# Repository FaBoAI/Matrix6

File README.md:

# Matrix Six

ESP32-S3-WROOM-1-N8R8を使った、Matrix5シールド向けのKiCad 10開発基板です。現行設計は **v0.8（2層・四隅R2 mm）**。内層配線を表裏へ移し、USBとGNDを再設計しました。オートルーターは使わず、部品配置と配線を個別に指定しています。

## KiCadで開く

[Matrix6.kicad_pro](hardware/Matrix6/Matrix6.kicad_pro)をKiCad 10で開いてください。KiCad標準のシンボル・フットプリント・3Dモデルライブラリをインストールし、同じフォルダーの `DevBoard.pretty` と `fp-lib-table` を一緒に保管します。動作確認版はKiCad 10.0.6です。

- ESP32-S3-WROOM-1-N8R8、ネイティブUSB-C、TPS63001によるUSB／LiPo両対応3.3 V電源。
- 裏面microSD（CS=10、MOSI=11、CLK=12、MISO=13）。口はアンテナ側へ向け、15.8 × 22.5 mmの抜き差し空間を確保。
- 裏面JST-PH 2ピンLiPo端子、MCP73831で公称100 mA充電、AO3401AによるUSB／電池自動切替。
- USBの左にRESET、右にBOOT。基板下部の赤LEDは `POWER`、青LEDはGPIO48の `PIN 48`。
- 40.64 × 61.00 mm、四隅R2 mm、2層FR4・公称1.6 mm・両面1 oz。USBは表面のみ・ビア0。表面のUSB両脇にGNDを確保し、表裏のGNDベタをビアで接続。
- H1/H2は各20ピン、ピッチ2.54 mm、列間33.02 mmのメスソケット。1番ピンはUSB側。
- 表面中央に大きな `Matrix Six`（文字高2.0 mm）、その直下に `Designed by GPT-6 Astra`（0.8 mm）。

## Matrix5シールドとの互換性

[Matrix5](https://github.com/FaBoAI/Matrix5)のMainとS1〜S11の実設計から端子情報を読み取り、全40位置と各シールドの使用信号を照合しました。**38端子の割り当てを合わせ、H2.20はVBAT**です。H2.5 / H2.6はNC（Matrix5のUSB D− / D＋）で、確認した11シールドはいずれも使用していません。

[端子表・シールド別照合・取り付け条件](docs/matrix5-compatibility.md)を参照してください。XY位置と使用ピンは一致していますが、積層高さ、アンテナ周辺、通電動作は実機での確認が必要です。USB-UART機能は追加していません。SDはシールドのSPI/I2C用GPIO11〜13を共有するため、競合する使い方ではカードを抜いてください。

電源計算の条件は周囲50℃、**3.3 V合計500 mA（MCU・SDを含む）＋VBUSシールド負荷100 mA＋充電100 mA**です。H1.1/H2.1は出力専用で、H2.1へ外部給電するとUSBへ逆給電できます。大電流のLED全点灯・コイル・ヒーターはこの条件に含みません。GPIOは3.3 Vで、S1用5 Vレベル変換はありません。

LiPoは保護回路付き1セル3.7 V／満充電4.2 V、500 mAh以上・放電定格1 A以上を基準とします。J3は**1番BAT+、2番GND**。同じJST形状でも電池側の極性を確認してください。電池動作中のH2.1に5 Vは出ません。セル温度センサーは搭載していません。

## 検証と図面

| 項目 | 保存したv0.8の結果 |
|---|---|
| DRC / ERC / 未配線 / 回路図整合性 | すべて0件 |
| 外形 | 四隅R2 mm、直線4本＋円弧4本で閉じた輪郭 |
| SD抜き差し空間 | 裏面15.8 × 22.5 mm、部品の配置禁止領域。重なり0 |
| Matrix5端子照合 | 全11シールドの使用ピン・40位置が一致 |
| USB | 表面のみ・ビア0、A/B両側とも幾何学的な長さ差0.01 mm未満 |
| USB本体下 | 表面配線・ビア・ベタ0。禁止領域の負の試験でも検出を確認 |
| USB直線部の表面GND | 両脇の幅0.5 mmを各1,563点検査、欠損0 |
| 電源降下の計算 | 3.3 V・500 mAでモジュールまで49.9 mV、H1まで27.9 mV |
| GND帰路のDC計算 | モジュール帰路500 mAで2.34 mV、入力帰路800 mAで6.45 mV |
| 最小ドリル | 0.3 mm。U1放熱穴はパッド0.8 mm、環状幅0.25 mm |

- [回路図](docs/validation/schematic.png) / [表面配線](docs/validation/pcb-top.png) / [裏面配線](docs/validation/pcb-bottom.png) / [SD抜き差し図](docs/validation/sd-access.svg)
- [DRC](docs/validation/drc.json) / [ERC](docs/validation/erc.json) / [シールド照合](docs/validation/matrix5-compatibility.json)
- [USB禁止領域](docs/validation/usb-keepout-validation.json) / [配線・電源計算](docs/validation/electrical-audit.json) / [GND計算](docs/validation/ground-plane-dc.json)
- [2層化の設計・検証範囲](docs/matrix-six-v08.md) / [USB断面計算](docs/analysis/two-layer-usb.json) / [表面GND検査](docs/validation/two-layer-ground.json)
- [検証対象CADのSHA-256](docs/validation/cad-sha256.json) / [回路図と30°3Dの並列表示](docs/validation/schematic-and-3d.png)

USBの均一断面は幅0.38 mm・線間0.18 mm・表面GNDとの間隔0.20 mm。FR4のεr=4.5を仮定した2D計算は約90.3 Ωです。裏面GNDは信号配線で4領域に分かれ、表面とビアで接続されており、連続した裏面参照プレーンではありません。USBの主な帰路は表面の両脇GNDとして設計しています。A側の長さにはR11のパッド間1.65 mmを含みます。

JLCPCB標準2層での管理インピーダンス保証は前提にしていません。断面・DC・配線温度の結果は設計計算であり、局所的な曲がりや長さ調整、コネクタを含むUSBの実測保証ではありません。試作機でUSB両挿し向き、SI/EMC、SD同時動作、給電切替・負荷・温度を確認します。

## JLCPCBへの試作発注

[v0.8の2層版製造データ](manufacturing/v0.8/README.md)を使用してください。48部品・26 BOMグループの型番は継承していますが、部品移動と表裏変更があるため **CPLもv0.8へ差し替えが必要**です。U1/U2等の放熱・パッド内ビアには充填と銅キャップを要求しており、両面実装費も残ります。最終削減額は新しい見積もりで確認してください。

既存のv0.7注文は4層版のデータです。v0.8の製造データとの混用はできません。部品在庫、実装位置・極性、CAMの確認が必要で、この作業では支払い・製造承認は行っていません。

JLCPCBに見積時点のGerberをアップロードし、基板5枚のWeb表示額は **$83.27**（部品・実装・送料別）でした。旧4層注文の$120.47から約31%減ですが、条件を最適化した4層比較額$86.68との差は約4%です。[見積もり内訳と条件](docs/analysis/two-layer-v08-quote.md)

## 検証の再実行

```sh
python3 scripts/verify_project.py
```

リポジトリをgit cloneして実行してください。設計ルール・互換性・外形の比較にはgit履歴が必要です。KiCad CLIと `pcbnew` / `wx` を使えるPythonが必要です。macOSの標準KiCadインストールは自動選択します。他の環境では `KICAD_CLI` と `KICAD_PYTHON` を指定してください。`ANALYSIS_PYTHON` にNumPy / SciPy / Shapely / Matplotlibを導入したPythonを指定すると、表裏を接続したGNDのDC計算も再実行します。検証はゾーンを再充填してPCBを保存し、レポートを更新するため、GUI上の編集を先に保存してください。

`scripts/manual_matrix5_layout.py` は初期インポートのコミットを入力とした、座標指定による移行記録です。オートルーターではありません。再実行すると後からのCAD編集を上書きするので、通常の検証には使いません。

v0.6の回路選定・電源条件は [設計メモ](docs/matrix-six-v06.md) に記録しています。

v0.7の外形変更は `scripts/round_board_corners.py`、v0.8の2層化は `scripts/redesign_two_layer.py` と `scripts/two_layer_routes.py` に記録しています。後者は `f12c10f` の4層CADから座標指定の変更を再生し、現在のCADを上書きするため通常の検証には使いません。v0.8の [外形検証](docs/validation/rounded-corners.json) はR2輪郭の保持と0.3 mm最小穴を確認します。版別の製造出力はPCBのリビジョンから出力先を決定します。

旧DevBoardの資料は [docs/devboard-v04](docs/devboard-v04/README.md) に履歴として保存しています。現在の端子・給電条件はこのREADMEとv0.6の互換性資料を使用してください。ライブラリの帰属は [THIRD_PARTY_NOTICES.md](THIRD_PARTY_NOTICES.md) に記載しています。

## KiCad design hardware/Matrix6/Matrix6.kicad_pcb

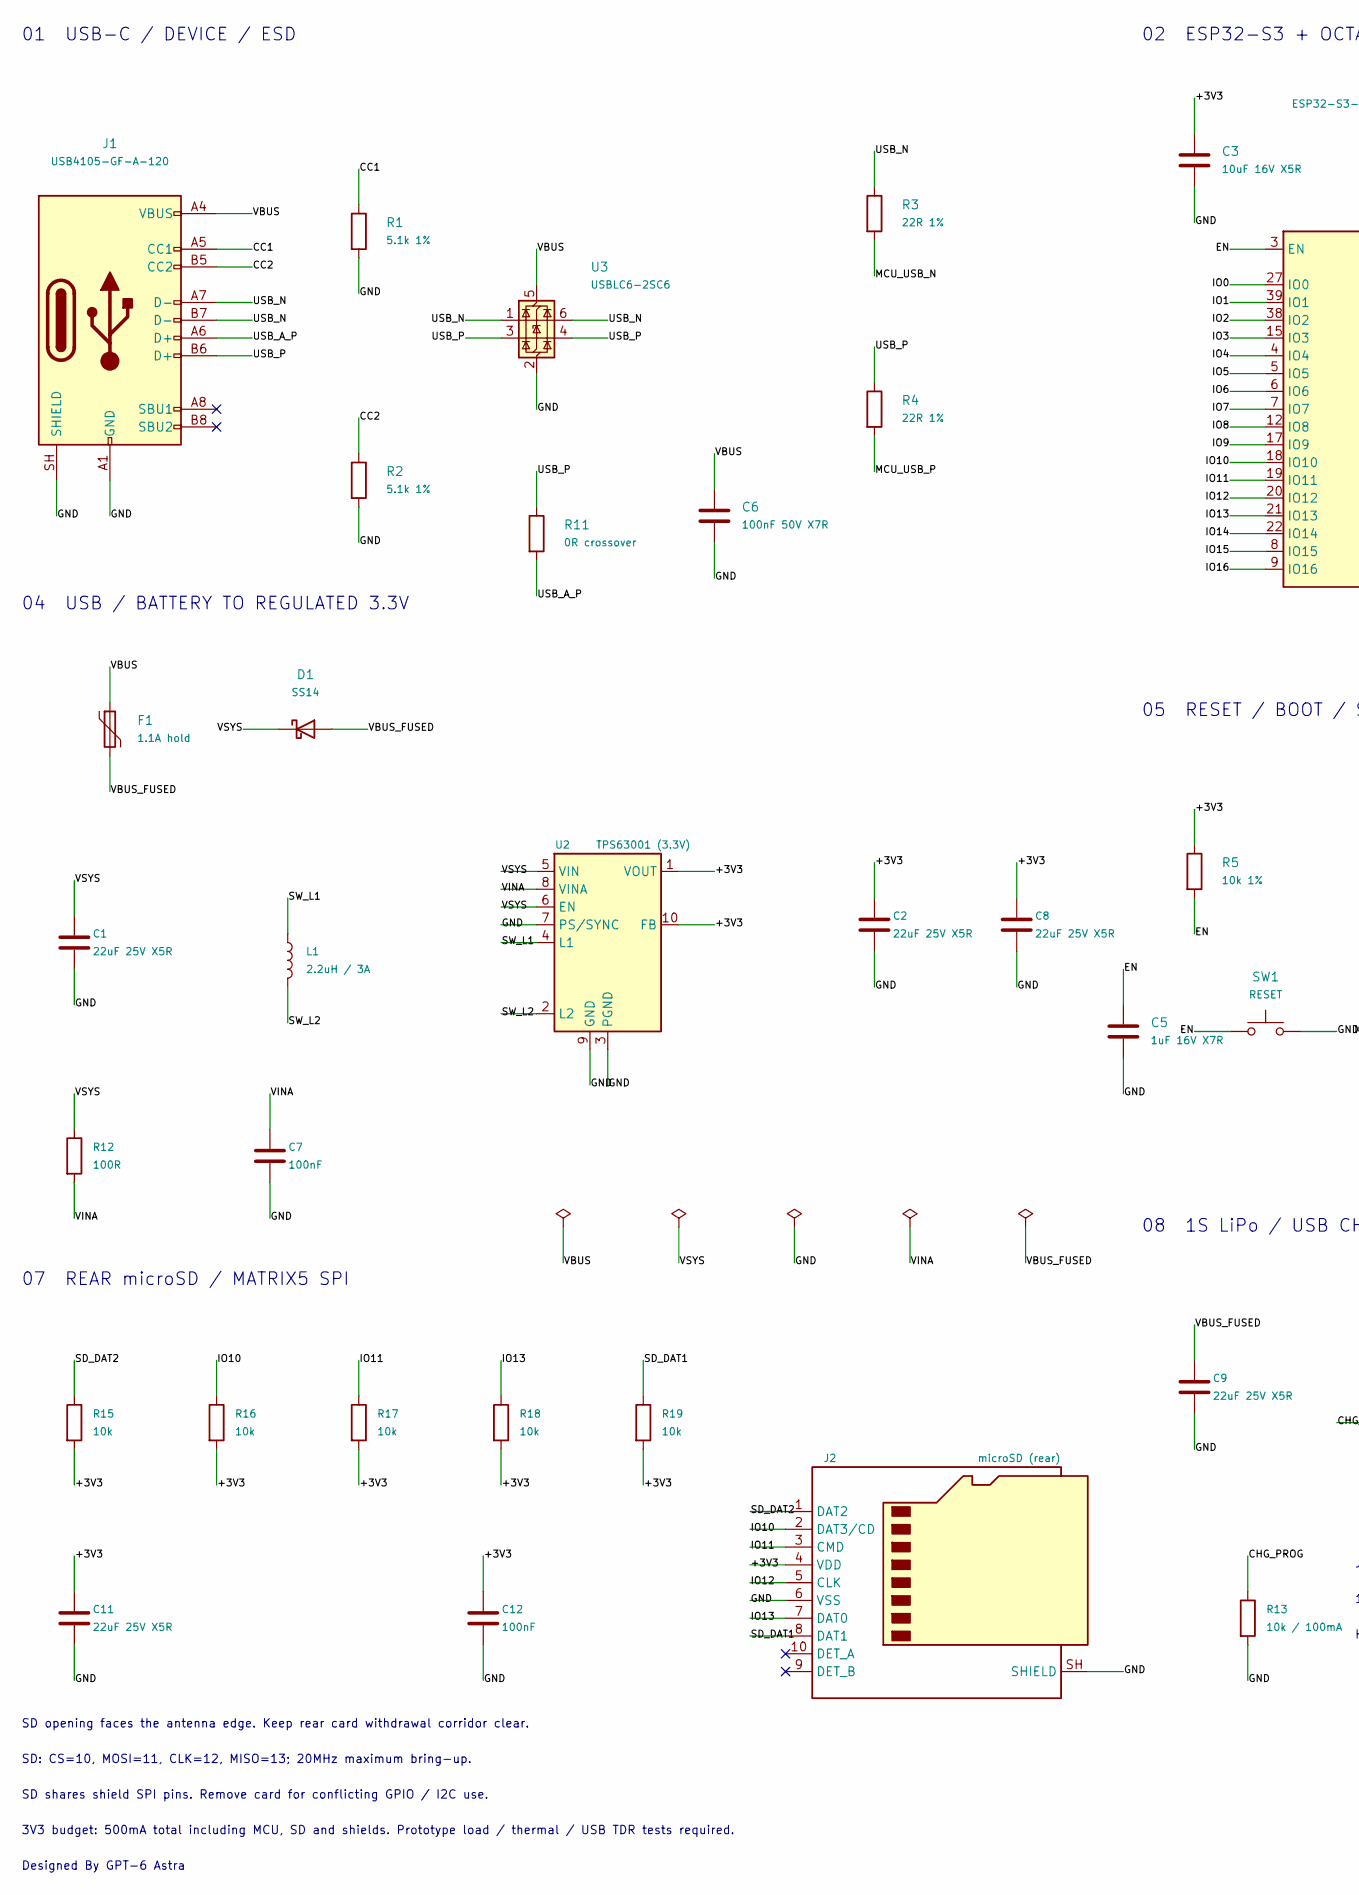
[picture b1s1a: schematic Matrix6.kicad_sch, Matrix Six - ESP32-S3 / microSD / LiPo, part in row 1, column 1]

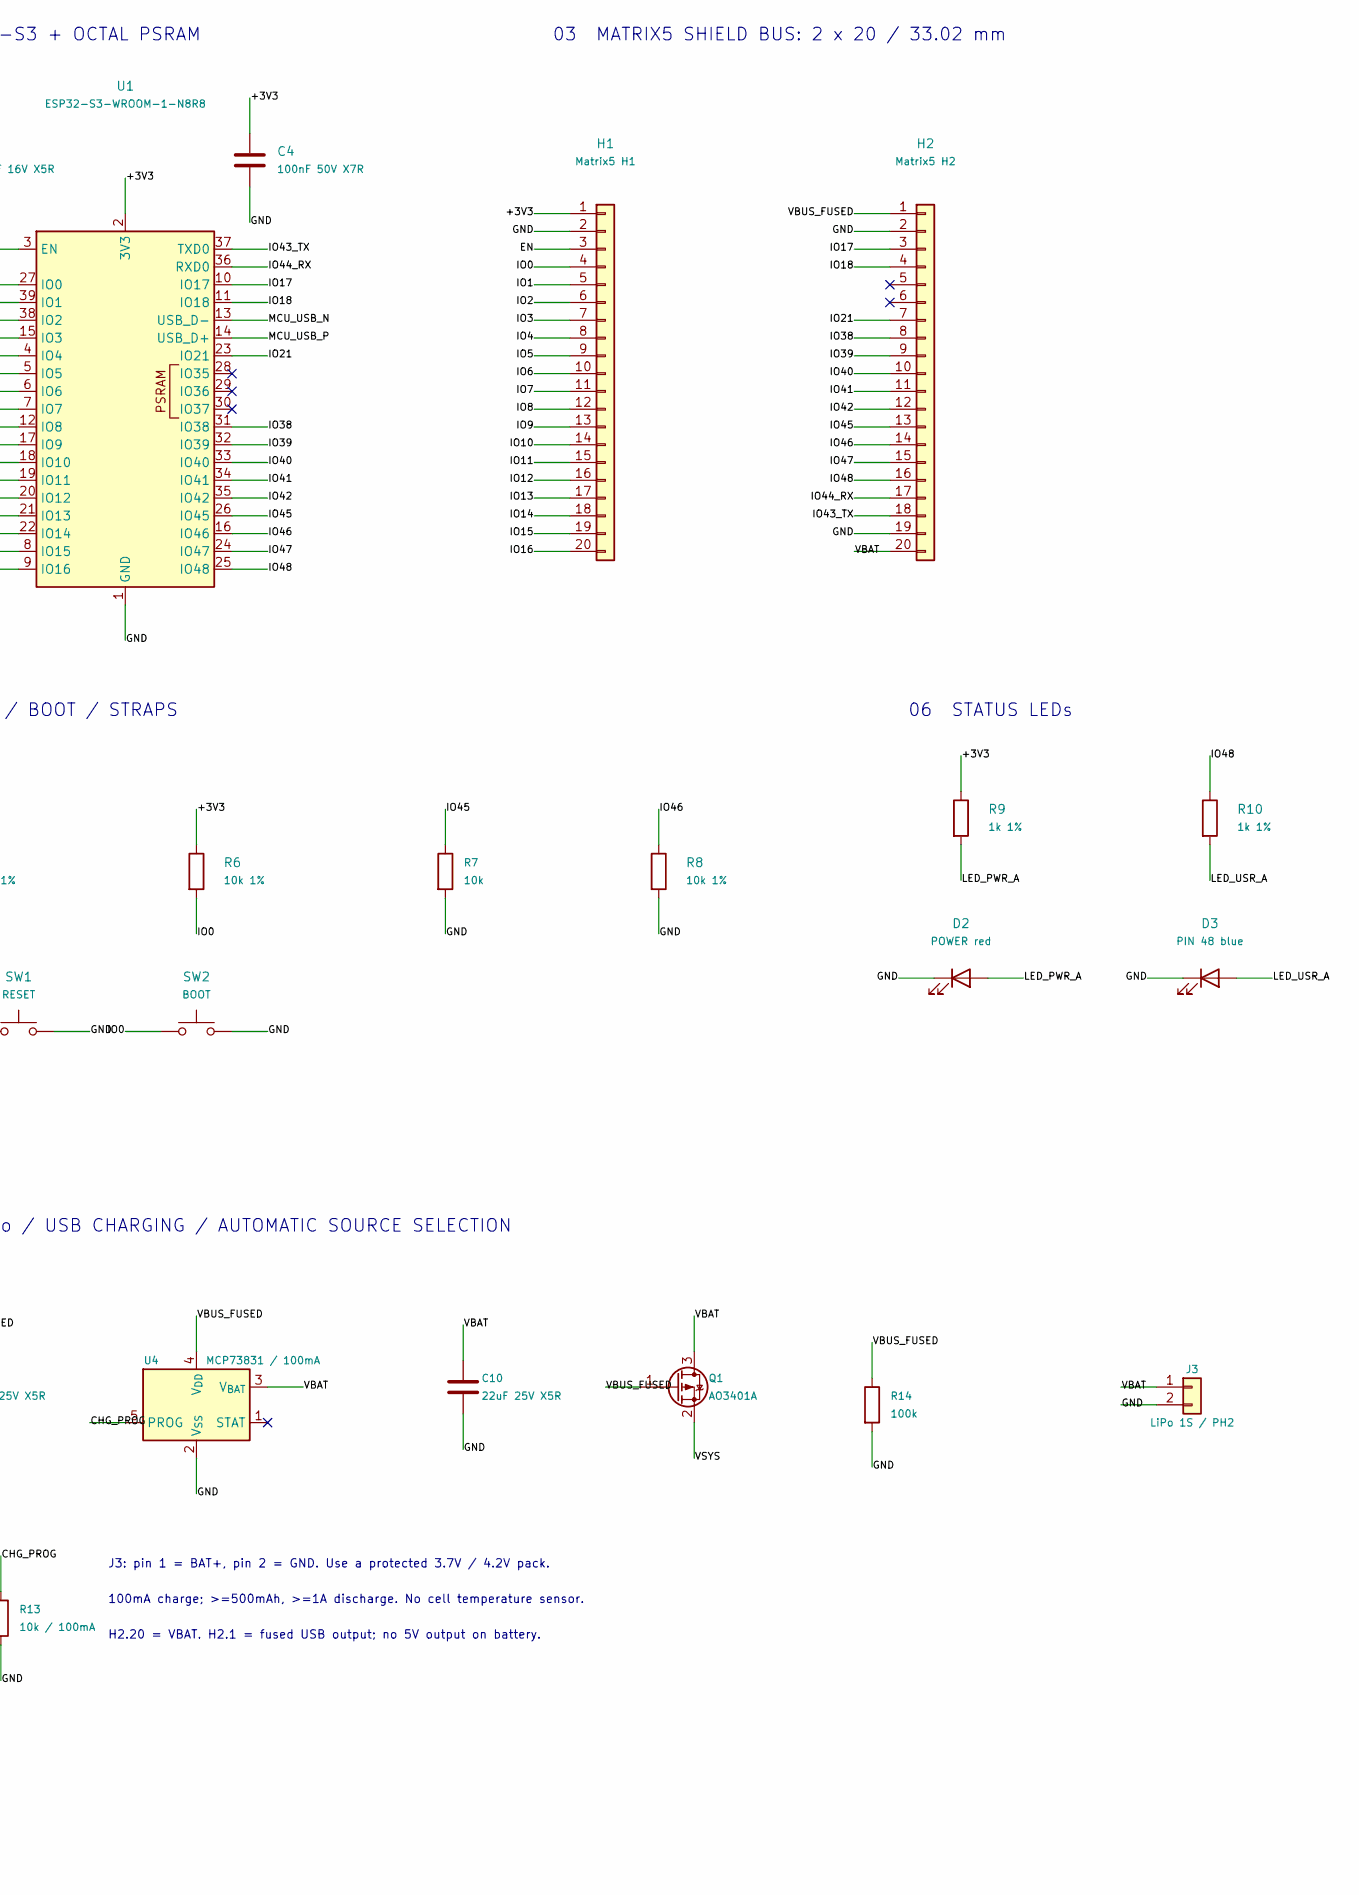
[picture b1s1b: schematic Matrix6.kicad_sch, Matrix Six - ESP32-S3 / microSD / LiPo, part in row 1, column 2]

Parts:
C1, C2, C8, C9, C10, C11: 22uF 25V X5R; C_0805_2012Metric; MPN CL21A226MAQNNNE; LCSC C45783
C3: 10uF 16V X5R; C_0805_2012Metric
C4, C6: 100nF 50V X7R; C_0603_1608Metric
C5: 1uF 16V X7R; C_0603_1608Metric
C7, C12: 100nF; C_0603_1608Metric
D1: SS14; D_SMA; MPN SS14-E3/61T
D2: POWER red; LED_0603_1608Metric
D3: PIN 48 blue; LED_0603_1608Metric
F1: 1.1A hold; Fuse_1206_3216Metric; MPN MF-NSMF110/16X-2
H1: Matrix5 H1; PinSocket_1x20_P2.54mm_Vertical
H2: Matrix5 H2; PinSocket_1x20_P2.54mm_Vertical
J1: USB4105-GF-A-120; USB4105_NoUnderbodyCopper
J2: microSD (rear); microSD_HC_Hirose_DM3AT-SF-PEJM5; MPN DM3AT-SF-PEJM5; LCSC C114218
J3: LiPo 1S / PH2; JST_PH_S2B-PH-K_1x02_P2.00mm_Horizontal; MPN S2B-PH-K-S(LF)(SN); LCSC C173752
L1: 2.2uH / 3A; L_Bourns-SRN4018; MPN SRN4018-2R2M; LCSC C913207
Q1: AO3401A; SOT-23; MPN AO3401A; LCSC C15127
R1, R2: 5.1k 1%; R_0603_1608Metric
R3, R4: 22R 1%; R_0603_1608Metric
R5, R6, R8: 10k 1%; R_0603_1608Metric
R7, R15, R16, R17, R18, R19: 10k; R_0603_1608Metric; MPN 0603WAF1002T5E; LCSC C25804
R9, R10: 1k 1%; R_0603_1608Metric
R11: 0R crossover; R_0603_1608Metric; MPN CRCW06030000Z0EA
R12: 100R; R_0603_1608Metric; MPN 0603WAF1000T5E; LCSC C22775
R13: 10k / 100mA; R_0603_1608Metric; MPN 0603WAF1002T5E; LCSC C25804
R14: 100k; R_0603_1608Metric; MPN 0603WAF1003T5E; LCSC C25803
SW1: RESET; SW_SPST_B3U-1000P
SW2: BOOT; SW_SPST_B3U-1000P
U1: ESP32-S3-WROOM-1-N8R8; ESP32-S3-WROOM-1_Edge
U2: TPS63001 (3.3V); Texas_DRC0010J; MPN TPS63001DRCR; LCSC C28060
U3: USBLC6-2SC6; SOT-23-6
U4: MCP73831 / 100mA; SOT-23-5; MPN MCP73831T-2ACI/OT; LCSC C424093

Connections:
/+3V3: C2.1, C3.1, C4.1, C8.1, C11.1, C12.1, H1.1, J2.4 (VDD), R5.1, R6.1, R9.1, R15.2, R16.2, R17.2, R18.2, R19.2, U1.2 (3V3), U2.1 (VOUT), U2.10 (FB)
/CC1: J1.A5 (CC1), R1.1
/CC2: J1.B5 (CC2), R2.1
/CHG_PROG: R13.1, U4.5 (PROG)
/EN: C5.1, H1.3, R5.2, SW1.1, U1.3 (EN)
/GND: C1.2, C2.2, C3.2, C4.2, C5.2, C6.2, C7.2, C8.2, C9.2, C10.2, C11.2, C12.2, D2.1 (K), D3.1 (K), H1.2, H2.2, H2.19, J1.A1 (GND), J1.A12 (GND), J1.B1 (GND), J1.B12 (GND), J1.SH (SHIELD), J2.6 (VSS), J2.SH (SHIELD), J3.2, R1.2, R2.2, R7.2, R8.2, R13.2, R14.2, SW1.2, SW2.2, U1.1 (GND), U1.40 (GND), U1.41 (GND), U2.3 (PGND), U2.7 (PS/SYNC), U2.9 (GND), U2.11 (PGND), U3.2 (GND), U4.2 (V_{SS})
/IO0: H1.4, R6.2, SW2.1, U1.27 (IO0)
/IO1: H1.5, U1.39 (IO1)
/IO2: H1.6, U1.38 (IO2)
/IO3: H1.7, U1.15 (IO3)
/IO4: H1.8, U1.4 (IO4)
/IO5: H1.9, U1.5 (IO5)
/IO6: H1.10, U1.6 (IO6)
/IO7: H1.11, U1.7 (IO7)
/IO8: H1.12, U1.12 (IO8)
/IO9: H1.13, U1.17 (IO9)
/IO10: H1.14, J2.2 (DAT3/CD), R16.1, U1.18 (IO10)
/IO11: H1.15, J2.3 (CMD), R17.1, U1.19 (IO11)
/IO12: H1.16, J2.5 (CLK), U1.20 (IO12)
/IO13: H1.17, J2.7 (DAT0), R18.1, U1.21 (IO13)
/IO14: H1.18, U1.22 (IO14)
/IO15: H1.19, U1.8 (IO15)
/IO16: H1.20, U1.9 (IO16)
/IO17: H2.3, U1.10 (IO17)
/IO18: H2.4, U1.11 (IO18)
/IO21: H2.7, U1.23 (IO21)
/IO38: H2.8, U1.31 (IO38)
/IO39: H2.9, U1.32 (IO39)
/IO40: H2.10, U1.33 (IO40)
/IO41: H2.11, U1.34 (IO41)
/IO42: H2.12, U1.35 (IO42)
/IO43_TX: H2.18, U1.37 (TXD0)
/IO44_RX: H2.17, U1.36 (RXD0)
/IO45: H2.13, R7.1, U1.26 (IO45)
/IO46: H2.14, R8.1, U1.16 (IO46)
/IO47: H2.15, U1.24 (IO47)
/IO48: H2.16, R10.1, U1.25 (IO48)
/LED_PWR_A: D2.2 (A), R9.2
/LED_USR_A: D3.2 (A), R10.2
/MCU_USB_N: R3.2, U1.13 (USB_D-)
/MCU_USB_P: R4.2, U1.14 (USB_D+)
/SD_DAT1: J2.8 (DAT1), R19.1
/SD_DAT2: J2.1 (DAT2), R15.1
/SW_L1: L1.1, U2.4 (L1)
/SW_L2: L1.2, U2.2 (L2)
/USB_A_P: J1.A6 (D+), R11.2
/USB_N: J1.A7 (D-), J1.B7 (D-), R3.1, U3.1 (I/O1), U3.6 (I/O1)
/USB_P: J1.B6 (D+), R4.1, R11.1, U3.3 (I/O2), U3.4 (I/O2)
/VBAT: C10.1, H2.20, J3.1, Q1.3 (D), U4.3 (V_{BAT})
/VBUS: C6.1, F1.1, J1.A4 (VBUS), J1.A9 (VBUS), J1.B4 (VBUS), J1.B9 (VBUS), U3.5 (VBUS)
/VBUS_FUSED: C9.1, D1.2 (A), F1.2, H2.1, Q1.1 (G), R14.1, U4.4 (V_{DD})
/VINA: C7.1, R12.2, U2.8 (VINA)
/VSYS: C1.1, D1.1 (K), Q1.2 (S), R12.1, U2.5 (VIN), U2.6 (EN)

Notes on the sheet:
01 USB-C / DEVICE / ESD
02 ESP32-S3 + OCTAL PSRAM
03 MATRIX5 SHIELD BUS: 2 x 20 / 33.02 mm
04 USB / BATTERY TO REGULATED 3.3V
05 RESET / BOOT / STRAPS
06 STATUS LEDs
07 REAR microSD / MATRIX5 SPI
08 1S LiPo / USB CHARGING / AUTOMATIC SOURCE SELECTION
J3: pin 1 = BAT+, pin 2 = GND. Use a protected 3.7V / 4.2V pack.
100mA charge; >=500mAh, >=1A discharge. No cell temperature sensor.
H2.20 = VBAT. H2.1 = fused USB output; no 5V output on battery.
SD: CS=10, MOSI=11, CLK=12, MISO=13; 20MHz maximum bring-up.
SD shares shield SPI pins. Remove card for conflicting GPIO / I2C use.
3V3 budget: 500mA total including MCU, SD and shields. Prototype load / thermal / USB TDR tests required.
Designed By GPT-6 Astra
SD opening faces the antenna edge. Keep rear card withdrawal corridor clear.

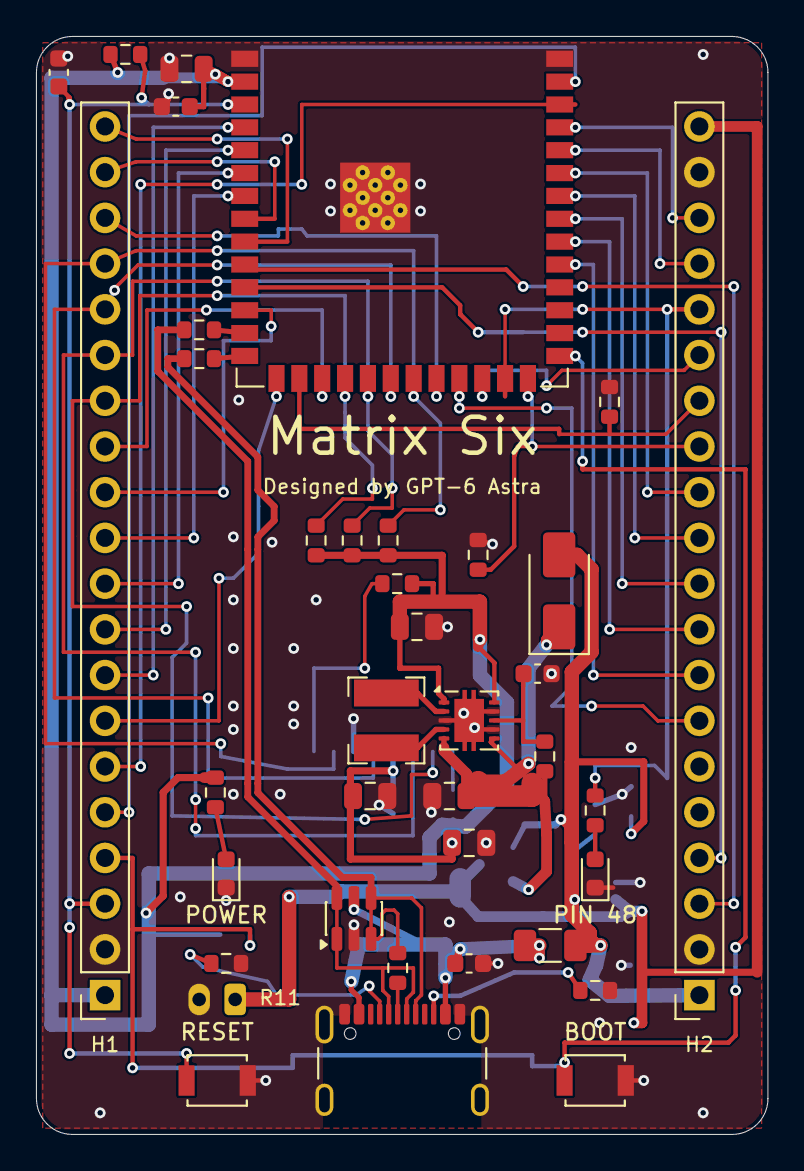
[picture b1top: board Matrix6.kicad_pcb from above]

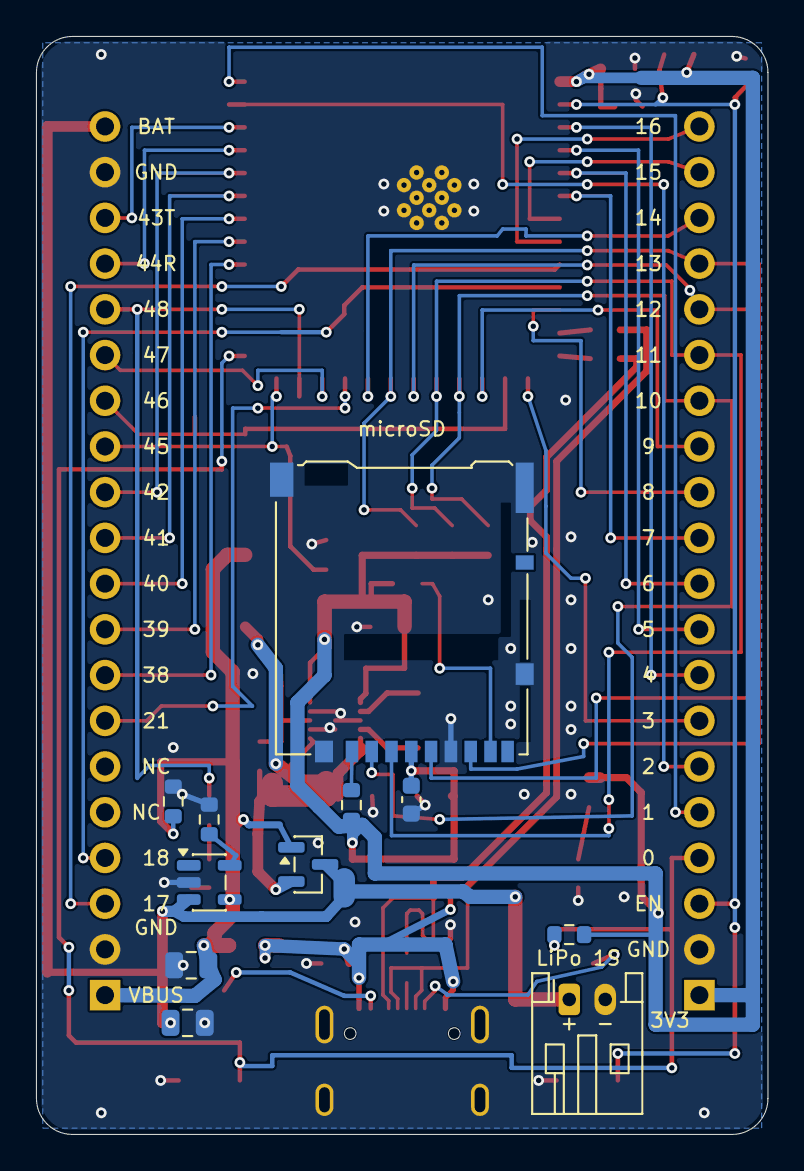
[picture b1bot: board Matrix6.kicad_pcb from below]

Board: 2 copper layers, 40.6 x 61.0 mm, 48 parts (11 on the bottom side), 53 nets.

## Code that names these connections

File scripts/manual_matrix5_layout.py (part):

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    s=fanouts[name];y={'IO10':120.9,'IO12':114.57,'IO13':112.1,'IO15':106.96,'IO16':105.7}.get(name,pad('H1',pin)[1]);path(name,[s,(s[0],y)]);via(name,(s[0],y));path(name,[(s[0],y),(103.0,y),pad('H1',pin)],p.In2_Cu)

# Right column: nested source fan-outs on B.Cu and separate horizontal exits.
for name,lane,pin in [('IO38',128.4,8),('IO39',129.3,9),('IO40',130.0,10),('IO41',130.7,11),('IO42',131.4,12),('IO44_RX',132.1,17),('IO43_TX',132.8,18)]:
    s=fanouts[name];y=pad('H2',pin)[1];path(name,[s,(lane,s[1]),(lane,y)]);via(name,(lane,y));path(name,[(lane,y),pad('H2',pin)],p.In2_Cu)
for name,lane,pin in [('IO17',136.2,3),('IO18',135.5,4)]:
    s=fanouts[name];y=pad('H2',pin)[1];path(name,[s,(lane,s[1])],p.In2_Cu);via(name,(lane,s[1]));path(name,[(lane,s[1]),(lane,y)]);via(name,(lane,y));path(name,[(lane,y),pad('H2',pin)],p.In2_Cu)
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        elif d.GetText()=='N8R8  v0.4':d.SetText('N8R8  v0.5')
for ref,x in [('H1',104.1),('H2',131.45)]:
    for i,name in enumerate(MAP[ref],1):
        label={'VBUS_FUSED':'VBUS','+3V3':'3V3','IO44_RX':'44R','IO43_TX':'43T'}.get(name,name or 'NC')
        if label.startswith('IO'):label=label[2:]
        t=p.PCB_TEXT(b);t.SetText(label);t.SetPosition(pt(x,pad(ref,i)[1]));t.SetLayer(p.B_SilkS);t.SetMirrored(True);t.SetTextSize(pt(.8,.8));t.SetTextThickness(mm(.12));b.Add(t)
b.GetTitleBlock().SetTitle('Matrix6 - ESP32-S3 / Matrix5 shield interface');b.GetTitleBlock().SetRevision('0.5')
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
